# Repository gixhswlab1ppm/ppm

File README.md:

# Summary
Table tennis can be an expensive sport to learn, with the quality and costs of coaches being hard to determine. Our project aims to make it easier and cheaper to learn table tennis. Our design objective is to create a hardware device that can be connected to a table tennis paddle and be used for various training purposes. Our first objective is to ensure that we can collect useful data. One way in which we will test that is by using unsupervised learning to help users mimic each other, like you might find with a coach and trainee. Our ending objective is to classify different gestures and moves, then to use that data for more complex learning to help users train independently of a coach through real time feedback and post-training analysis through a web interface.
 
# Statement of Problem
Table tennis (commonly referred to as “ping pong”) is an Olympic sport, and a difficult one to learn on a professional level; some countries only have a handful of professional players, and they tend to have played for a long time, taking lessons for 5-15 years (source). Lessons from professional coaches can cost anywhere from $20-100, and there are a wide number of attacking and defensive strokes that players must learn, as well as transitions from each stroke to the other (source). Approximately 19 million Americans play table tennis (source), but only 9000 Americans are registered in the national semi-professional organization (source). This means that almost all table tennis players in the United States have not had professional training.

# Technical Documentation
It's using Python and Arduino/Raspberry Pi. It does ML via sklearn, and data viz via matplotlib.

# Usage Instructions
Run the file

# Notes:
Manually measured swing-period:
cutuy_swing_walk 2s

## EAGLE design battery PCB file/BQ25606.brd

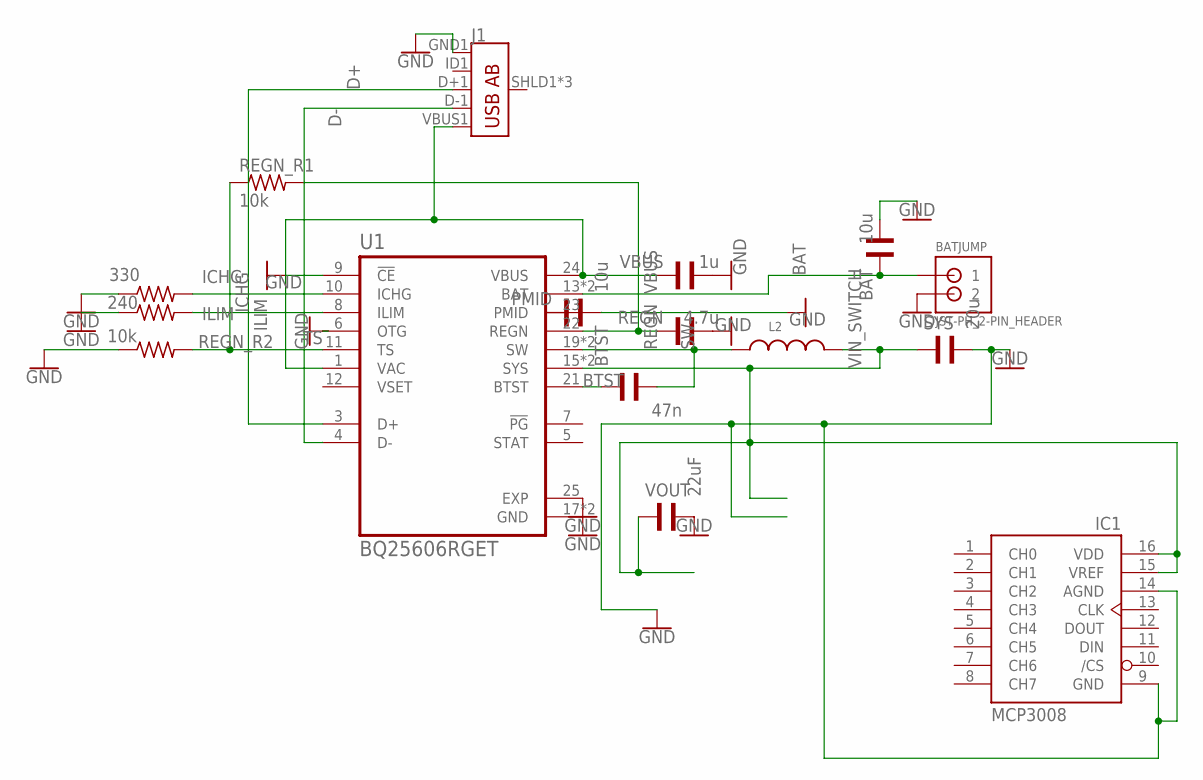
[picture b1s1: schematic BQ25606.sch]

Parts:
BAT: 10u; WCAP-CSMH_0805_REFLOW; MPN GRM21BR61E106KA73L
BATJUMP: JST-PH_2-PIN_HEADER; JST_B2B-PH_HEADER
BTST: 47n; WCAP-CSGP_0805_WAVE; MPN MC0805B473K500CT
IC1: MCP3008; DIL16
ICHG: 330; M0805; MPN RR1220P-331-D
ILIM: 240; M0805
J1: USB_AB_SMT; USB-AB-MICRO-SMD
L2: WE-PMI_0805_74479775215; WE-PMI_0805
PMID: 10u; WCAP-CSMH_0805_REFLOW; MPN C2012X5R1A226M125AB
REGN: 4.7u; WCAP-CSGP_0805_WAVE; MPN C2012X5R1H475K125AB
REGN_R1, REGN_R2: 10k; M0805; MPN ERJ-6ENF1002V
SYS: 20u; WCAP-CSMH_0805_REFLOW; MPN CC0402KRX5R6BB105
U1: BQ25606RGET; QFN50P400X400X100-25N270X270; MPN BQ25606RGET .
VBUS: 1u; WCAP-CSMH_0805_REFLOW; MPN MCTT21X105K160CT
VOUT: 22uF; WCAP-CSMH_0805_REFLOW; MPN CC0402KRX5R6BB105

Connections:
BAT: BAT.2, BATJUMP.P1 (1), U1.13 (BAT), U1.14 (BAT)
BTST: BTST.2, U1.21 (BTST)
D+: J1.D+1 (D+), U1.3 (D+)
D-: J1.D-1 (D-), U1.4 (D-)
GND: BAT.1, BATJUMP.P2 (2), IC1.9 (GND), IC1.14 (AGND), ICHG.1, ILIM.1, J1.GND1 (GND), PMID.1, REGN.1, REGN_R2.1, SYS.1, U1.6 (OTG), U1.9 (!CE), U1.17 (GND), U1.18 (GND), U1.25 (EXP), VBUS.1, VOUT.1
ICHG: ICHG.2, U1.10 (ICHG)
ILIM: ILIM.2, U1.8 (ILIM)
PMID: U1.23 (PMID)
REGN: REGN.2, REGN_R1.2, U1.22 (REGN)
SW: BTST.1, L2.1, U1.19 (SW), U1.20 (SW)
TS: REGN_R1.1, REGN_R2.2, U1.11 (TS)
VBUS: J1.VBUS1 (VBUS), U1.1 (VAC), U1.24 (VBUS), VBUS.2
VIN_SWITCH: IC1.15 (VREF), IC1.16 (VDD), L2.2, SYS.2, U1.15 (SYS), U1.16 (SYS), VOUT.2

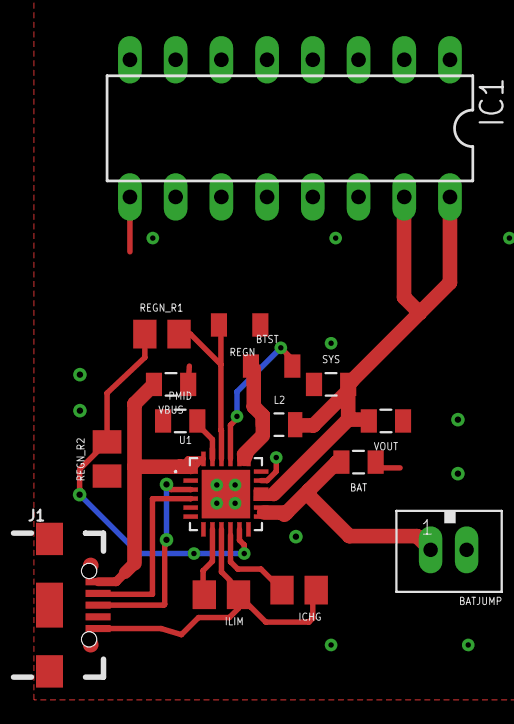
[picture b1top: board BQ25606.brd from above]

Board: 2 copper layers, 16 parts (0 on the bottom side), 12 nets.

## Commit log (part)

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2019-01-19 Impl FFT test
2019-01-19 Impl FFT test on single & multiple swings
2019-01-21 Beautify previous shity code; update visualization to include all 6 features
2019-01-21 Impl validation for hypothesis: spectrum consistency over diff time ranges
2019-01-24 Cirtical bug fix for timestamp alignment for raw data; impl period estimation; verify algorithm on swing+walk datasets; gather new datasets; add docs for fft function
2019-01-24 Minor changes before migrating to GitLab
2019-01-24 Impl polling for main period prediction
2019-01-24 Impl fft result recording across features & windows; fix bug in fft function
2019-01-26 arduino code for penziometer triangulation
2019-01-28 Test duplex over serial over USB between Arduino & Pi; impl data reporting from Arduino to Pi
2019-01-29 Add IMU + Piezo collected data; impl Pi code that emits file w/ respect to a switch on Arduino; impl simple swing counter
2019-01-30 Add pip3 dependencies
2019-01-31 Fix bug after Nano migration; move swing detection code to Pi
2019-01-31 triangulation code
2019-01-31 Cosmatic changes for M1 demo
2019-01-31 triangular 2d for position detecting
2019-02-07 Milestone 1 demo day hotfix - skipping topk count
2019-02-10 Add per-feature-level dedup logic for peak detection; add ts col in data packet; data normalization for IMU cols now *before* fft.
2019-02-10 Add per-epoch dumping for circular_buffer
2019-02-10 Update arduino code for new packet format; wrap swing_count, hit_detection as services; impl real-time pipeline
2019-02-11 Encapsulate fft as a real-time service; cleanup algorithm code
2019-02-11 Impl logic for hw button for activity start/end
2019-02-14 esp8266 module code
2019-02-14 Minor bug fixes & add tests for algorithm svcs
2019-02-15 Add lib for e-ink display manipulation; fix bug during dumping in circular_buffer; add sensor data for new dt.
2019-02-15 Minor bug fixes & add viz for algorithm; update req docs
2019-02-15 add web app template
2019-02-15 remove bad node nonsense
2019-02-15 new web-app
2019-02-16 data cleaning
2019-02-16 bar chart attempt, some bugs
2019-02-16 Prepare to migrate to Pi Zero; add zero-shifting data
2019-02-16 Improve folder structure readilibilty
2019-02-17 Add insight graphs; add viz for hit point feature; add raw data
2019-02-17 Impl ML dataset gen windowed by clustered data of piezo readings; minor naming changes
2019-02-18 Impl LSTM for swing-hit_cohesion regression; add viz during model testing
2019-02-19 Reimpl hit-point related svc to include hit cohesion score; improve display partial refresh & layout; add env toggle for (on-premise) Pi
2019-02-20 Add paddle design (Jason)
2019-02-21 node modules? (web app firebase read)
2019-02-21 fix web app
2019-02-21 jason changes
2019-03-03 Impl hit-disperity and hit-strength features; add support for multi-label regression in ML pipeline.
2019-03-04 Created using Colaboratory
2019-03-04 Formatted using Colaboratory
2019-03-07 add bar charts, truncate units, clean code, add login system
2019-03-08 Add writing for Task 1/2 in Final Report Part 1
2019-03-08 Proofread Task 3
2019-03-08 AWESOME CODE STYLE FIX
2019-03-08 Simplify ML model for correlation; impl multi-file training
2019-03-09 Improve boot-up speed and real-time capability; prep ui_state mgmt
2019-03-09 Add sensor data & resources; improve algorithm code readibility
2019-03-09 Impl profile logic; impl GUI logic for welcome, profile, and train screens
2019-03-09 added lots of visualization features, including displaying all raw data dynamically
2019-03-09 Unify dir path generation
2019-03-09 Generate tflite library & model; impl new ML model for tflite compatibility
2019-03-10 added file switching, raw data switching
2019-03-10 Improve threading parallelism and real-time responsiveness
2019-03-11 Fix duplicates caused by file name difference
2019-03-14 eagle pcb file and fusion 3d cad file
2019-03-14 Hotfix code for M3 prototype
2019-03-17 Update Task 3 & 4; finalizing the document
2019-03-17 final proofread
2019-03-20 Add files via upload
    poster file
2019-03-22 Proofread done - 2 todos left
2021-05-27 Bump y18n in /web-app/startbootstrap-sb-admin-gh-pages/functions
    Bumps [y18n](https://github.com/yargs/y18n) from 3.2.1 to 3.2.2.
    - [Release notes](https://github.com/yargs/y18n/releases)
    - [Changelog](https://github.com/yargs/y18n/blob/master/CHANGELOG.md)
    - [Commits](https://github.com/yargs/y18n/commits)
2021-05-27 Bump grpc in /web-app/startbootstrap-sb-admin-gh-pages/functions
    Bumps [grpc](https://github.com/grpc/grpc-node) from 1.18.0 to 1.24.10.
    - [Release notes](https://github.com/grpc/grpc-node/releases)
    - [Commits](https://github.com/grpc/grpc-node/compare/grpc@1.18.0...grpc@1.24.10)
2021-05-27 Bump browserslist in /web-app/startbootstrap-sb-admin-gh-pages
    Bumps [browserslist](https://github.com/browserslist/browserslist) from 4.4.1 to 4.16.6.
    - [Release notes](https://github.com/browserslist/browserslist/releases)
    - [Changelog](https://github.com/browserslist/browserslist/blob/main/CHANGELOG.md)
    - [Commits](https://github.com/browserslist/browserslist/compare/4.4.1...4.16.6)
2021-05-27 Bump hosted-git-info in /web-app/startbootstrap-sb-admin-gh-pages
    Bumps [hosted-git-info](https://github.com/npm/hosted-git-info) from 2.7.1 to 2.8.9.
    - [Release notes](https://github.com/npm/hosted-git-info/releases)
    - [Changelog](https://github.com/npm/hosted-git-info/blob/v2.8.9/CHANGELOG.md)
    - [Commits](https://github.com/npm/hosted-git-info/compare/v2.7.1...v2.8.9)
2021-05-27 Bump lodash in /web-app/startbootstrap-sb-admin-gh-pages
    Bumps [lodash](https://github.com/lodash/lodash) from 4.17.11 to 4.17.21.
    - [Release notes](https://github.com/lodash/lodash/releases)
    - [Commits](https://github.com/lodash/lodash/compare/4.17.11...4.17.21)
2021-06-15 Bump postcss in /web-app/startbootstrap-sb-admin-gh-pages
    Bumps [postcss](https://github.com/postcss/postcss) from 7.0.14 to 7.0.36.
    - [Release notes](https://github.com/postcss/postcss/releases)
    - [Changelog](https://github.com/postcss/postcss/blob/main/CHANGELOG.md)
    - [Commits](https://github.com/postcss/postcss/compare/7.0.14...7.0.36)
    ---
    updated-dependencies:
2021-08-04 Bump tar in /web-app/startbootstrap-sb-admin-gh-pages
    Bumps [tar](https://github.com/npm/node-tar) from 2.2.1 to 2.2.2.
    - [Release notes](https://github.com/npm/node-tar/releases)
    - [Changelog](https://github.com/npm/node-tar/blob/main/CHANGELOG.md)
    - [Commits](https://github.com/npm/node-tar/compare/v2.2.1...v2.2.2)
    ---
    updated-dependencies:
2021-08-10 Bump path-parse in /web-app/startbootstrap-sb-admin-gh-pages
    Bumps [path-parse](https://github.com/jbgutierrez/path-parse) from 1.0.6 to 1.0.7.
    - [Release notes](https://github.com/jbgutierrez/path-parse/releases)
    - [Commits](https://github.com/jbgutierrez/path-parse/commits/v1.0.7)
    ---
    updated-dependencies:
    - dependency-name: path-parse
2022-01-13 Bump follow-redirects in /web-app/startbootstrap-sb-admin-gh-pages
    Bumps [follow-redirects](https://github.com/follow-redirects/follow-redirects) from 1.6.1 to 1.14.7.
    - [Release notes](https://github.com/follow-redirects/follow-redirects/releases)
    - [Commits](https://github.com/follow-redirects/follow-redirects/compare/v1.6.1...v1.14.7)
    ---
    updated-dependencies:
    - dependency-name: follow-redirects
2022-02-10 Bump node-sass in /web-app/startbootstrap-sb-admin-gh-pages
    Bumps [node-sass](https://github.com/sass/node-sass) from 4.11.0 to 4.14.1.
    - [Release notes](https://github.com/sass/node-sass/releases)
    - [Changelog](https://github.com/sass/node-sass/blob/master/CHANGELOG.md)
    - [Commits](https://github.com/sass/node-sass/compare/v4.11.0...v4.14.1)
    ---
    updated-dependencies:
2022-02-11 Bump ajv in /web-app/startbootstrap-sb-admin-gh-pages
    Bumps [ajv](https://github.com/ajv-validator/ajv) from 6.7.0 to 6.12.6.
    - [Release notes](https://github.com/ajv-validator/ajv/releases)
    - [Commits](https://github.com/ajv-validator/ajv/compare/v6.7.0...v6.12.6)
    ---
    updated-dependencies:
    - dependency-name: ajv
2022-02-12 Bump follow-redirects in /web-app/startbootstrap-sb-admin-gh-pages
    Bumps [follow-redirects](https://github.com/follow-redirects/follow-redirects) from 1.6.1 to 1.14.8.
    - [Release notes](https://github.com/follow-redirects/follow-redirects/releases)
    - [Commits](https://github.com/follow-redirects/follow-redirects/compare/v1.6.1...v1.14.8)
    ---
    updated-dependencies:
    - dependency-name: follow-redirects
2022-04-09 Bump moment in /web-app/startbootstrap-sb-admin-gh-pages
    Bumps [moment](https://github.com/moment/moment) from 2.29.1 to 2.29.2.
    - [Release notes](https://github.com/moment/moment/releases)
    - [Changelog](https://github.com/moment/moment/blob/develop/CHANGELOG.md)
    - [Commits](https://github.com/moment/moment/compare/2.29.1...2.29.2)
    ---
    updated-dependencies:
2022-05-26 Bump ujson from 1.35 to 5.2.0
    Bumps [ujson](https://github.com/ultrajson/ultrajson) from 1.35 to 5.2.0.
    - [Release notes](https://github.com/ultrajson/ultrajson/releases)
    - [Commits](https://github.com/ultrajson/ultrajson/compare/v1.35...5.2.0)
    ---
    updated-dependencies:
    - dependency-name: ujson
2022-06-21 Bump numpy from 1.15.2 to 1.22.0
    Bumps [numpy](https://github.com/numpy/numpy) from 1.15.2 to 1.22.0.
    - [Release notes](https://github.com/numpy/numpy/releases)
    - [Changelog](https://github.com/numpy/numpy/blob/main/doc/HOWTO_RELEASE.rst)
    - [Commits](https://github.com/numpy/numpy/compare/v1.15.2...v1.22.0)
    ---
    updated-dependencies:
2022-07-05 Bump ujson from 1.35 to 5.4.0
    Bumps [ujson](https://github.com/ultrajson/ultrajson) from 1.35 to 5.4.0.
    - [Release notes](https://github.com/ultrajson/ultrajson/releases)
    - [Commits](https://github.com/ultrajson/ultrajson/compare/v1.35...5.4.0)
    ---
    updated-dependencies:
    - dependency-name: ujson
2022-07-07 Bump moment in /web-app/startbootstrap-sb-admin-gh-pages
    Bumps [moment](https://github.com/moment/moment) from 2.29.1 to 2.29.4.
    - [Release notes](https://github.com/moment/moment/releases)
    - [Changelog](https://github.com/moment/moment/blob/develop/CHANGELOG.md)
    - [Commits](https://github.com/moment/moment/compare/2.29.1...2.29.4)
    ---
    updated-dependencies:
2022-11-22 Bump engine.io and browser-sync
    Bumps [engine.io](https://github.com/socketio/engine.io) to 6.2.1 and updates ancestor dependency [browser-sync](https://github.com/BrowserSync/browser-sync). These dependencies need to be updated to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
    Updates `engine.io` from 3.2.1 to 6.2.1
    - [Release notes](https://github.com/socketio/engine.io/releases)
    - [Changelog](https://github.com/socketio/engine.io/blob/main/CHANGELOG.md)
    - [Commits](https://github.com/socketio/engine.io/compare/3.2.1...6.2.1)
    Updates `browser-sync` from 2.26.3 to 2.27.10
2022-12-02 Bump decode-uri-component in /web-app/startbootstrap-sb-admin-gh-pages
    Bumps [decode-uri-component](https://github.com/SamVerschueren/decode-uri-component) from 0.2.0 to 0.2.2.
    - [Release notes](https://github.com/SamVerschueren/decode-uri-component/releases)
    - [Commits](https://github.com/SamVerschueren/decode-uri-component/compare/v0.2.0...v0.2.2)
    ---
    updated-dependencies:
    - dependency-name: decode-uri-component
2022-12-09 Bump express in /web-app/startbootstrap-sb-admin-gh-pages/functions
    Bumps [express](https://github.com/expressjs/express) from 4.16.4 to 4.18.2.
    - [Release notes](https://github.com/expressjs/express/releases)
    - [Changelog](https://github.com/expressjs/express/blob/master/History.md)
    - [Commits](https://github.com/expressjs/express/compare/4.16.4...4.18.2)
    ---
    updated-dependencies:

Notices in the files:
parts and their libraries:
Wurth_Elektronik_Passive_Capacitors_rev1: Copyright: Würth Elektronik
SparkFun-Connectors: Licensing: Creative Commons ShareAlike 4.0 International - https://creativecommons.org/licenses/by-sa/4.0
